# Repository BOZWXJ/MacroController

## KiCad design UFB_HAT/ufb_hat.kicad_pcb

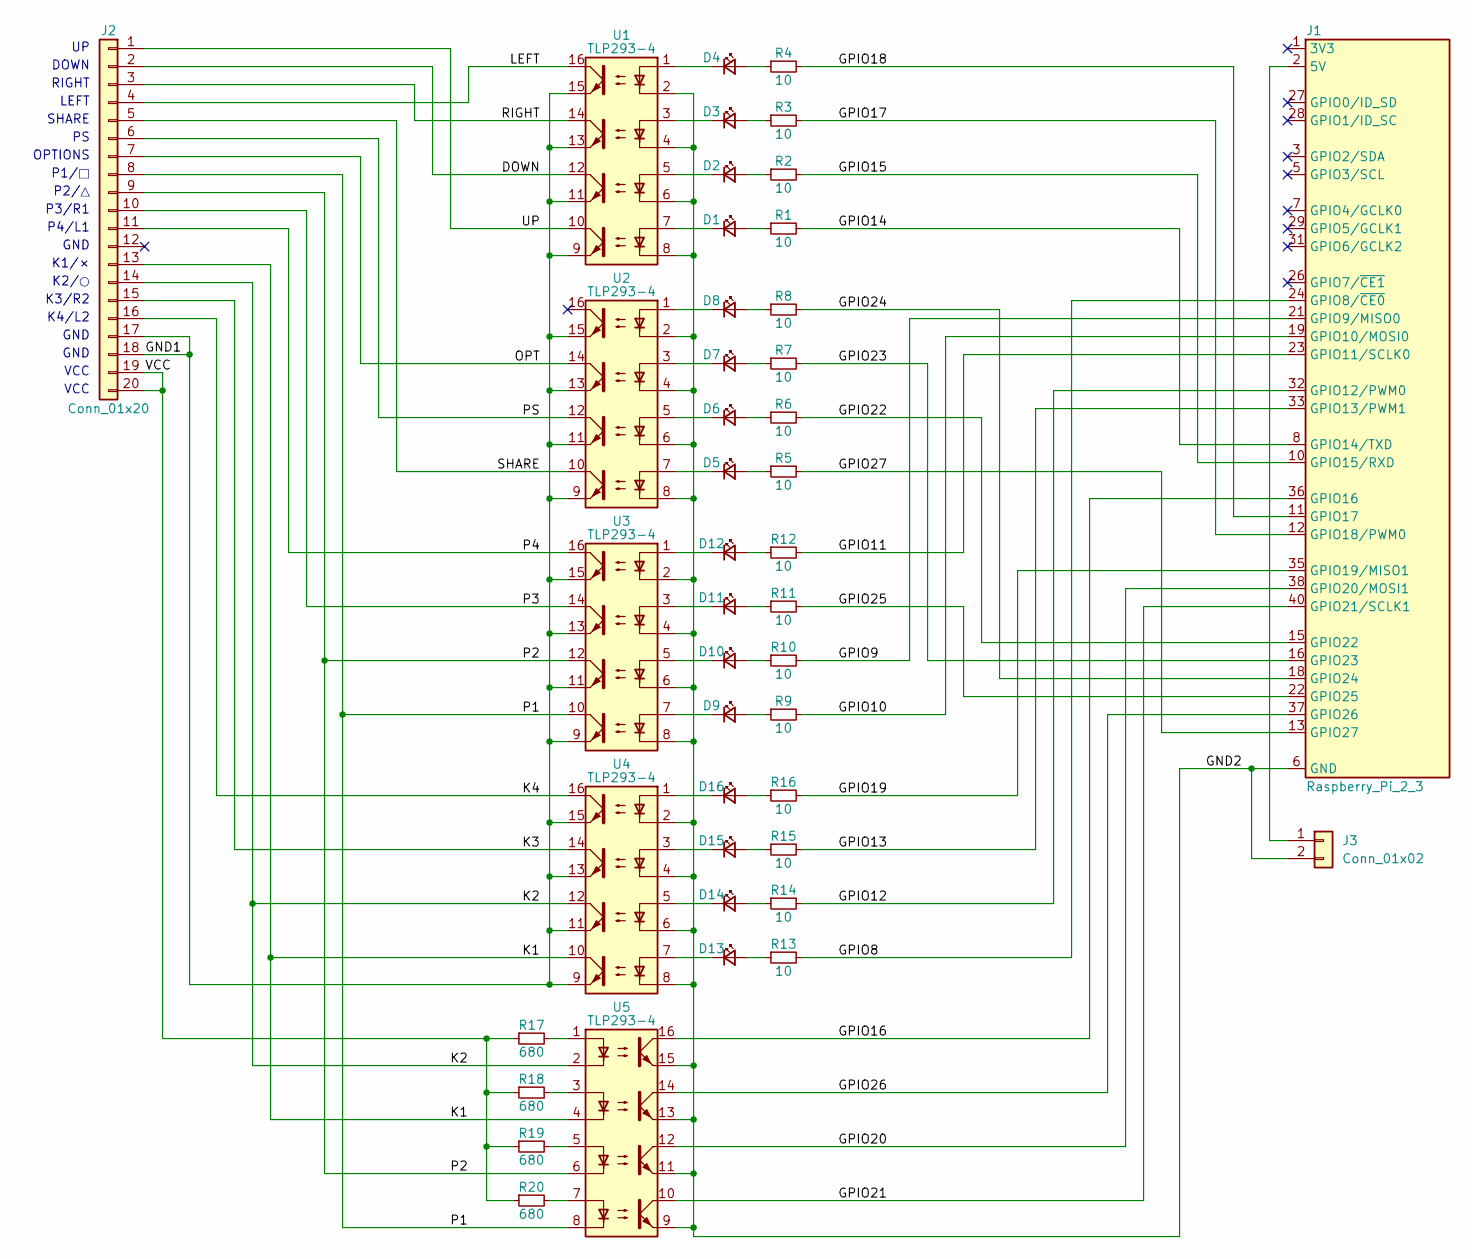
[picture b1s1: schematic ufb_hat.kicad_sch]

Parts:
D1, D2, D3, D4, D5, D6, D7, D8, D9, D10, D11, D12, D13, D14, D15, D16: LED_Small; LED_0603_1608Metric_Pad1.05x0.95mm_HandSolder
J1: Raspberry_Pi_2_3; PinSocket_2x20_P2.54mm_Vertical
J2: Conn_01x20; PinHeader_2x10_P2.54mm_Vertical
J3: Conn_01x02; PinHeader_1x02_P2.54mm_Vertical
R1, R2, R3, R4, R5, R6, R7, R8, R9, R10, R11, R12, R13, R14, R15, R16: 10; R_0603_1608Metric_Pad0.98x0.95mm_HandSolder
R17, R18, R19, R20: 680; R_0603_1608Metric_Pad0.98x0.95mm_HandSolder
U1, U2, U3, U4, U5: TLP293-4; SOIC-16_4.55x10.3mm_P1.27mm

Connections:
/DOWN: J2.2, U1.12
/GND1: J2.17, J2.18, U1.9, U1.11, U1.13, U1.15, U2.9, U2.11, U2.13, U2.15, U3.9, U3.11, U3.13, U3.15, U4.9, U4.11, U4.13, U4.15
/GND2: J1.6 (GND), J1.9 (GND), J1.14 (GND), J1.20 (GND), J1.25 (GND), J1.30 (GND), J1.34 (GND), J1.39 (GND), J3.2, U1.2, U1.4, U1.6, U1.8, U2.2, U2.4, U2.6, U2.8, U3.2, U3.4, U3.6, U3.8, U4.2, U4.4, U4.6, U4.8, U5.9, U5.11, U5.13, U5.15
/GPIO8: J1.24 (GPIO8/~CE0), R13.2
/GPIO9: J1.21 (GPIO9/MISO0), R10.2
/GPIO10: J1.19 (GPIO10/MOSI0), R9.2
/GPIO11: J1.23 (GPIO11/SCLK0), R12.2
/GPIO12: J1.32 (GPIO12/PWM0), R14.2
/GPIO13: J1.33 (GPIO13/PWM1), R15.2
/GPIO14: J1.8 (GPIO14/TXD), R1.2
/GPIO15: J1.10 (GPIO15/RXD), R2.2
/GPIO16: J1.36 (GPIO16), U5.16
/GPIO17: J1.12 (GPIO18/PWM0), R3.2
/GPIO18: J1.11 (GPIO17), R4.2
/GPIO19: J1.35 (GPIO19/MISO1), R16.2
/GPIO20: J1.38 (GPIO20/MOSI1), U5.12
/GPIO21: J1.40 (GPIO21/SCLK1), U5.10
/GPIO22: J1.15 (GPIO22), R6.2
/GPIO23: J1.16 (GPIO23), R7.2
/GPIO24: J1.18 (GPIO24), R8.2
/GPIO25: J1.22 (GPIO25), R11.2
/GPIO26: J1.37 (GPIO26), U5.14
/GPIO27: J1.13 (GPIO27), R5.2
/K1: J2.13, U4.10, U5.4
/K2: J2.14, U4.12, U5.2
/K3: J2.15, U4.14
/K4: J2.16, U4.16
/LEFT: J2.4, U1.16
/OPT: J2.7, U2.14
/P1: J2.8, U3.10, U5.8
/P2: J2.9, U3.12, U5.6
/P3: J2.10, U3.14
/P4: J2.11, U3.16
/PS: J2.6, U2.12
/RIGHT: J2.3, U1.14
/SHARE: J2.5, U2.10
/UP: J2.1, U1.10
/VCC: J2.19, J2.20, R17.1, R18.1, R19.1, R20.1
unnamed: D1.2 (A), R1.1
unnamed: D1.1 (K), U1.7
unnamed: D2.2 (A), R2.1
unnamed: D2.1 (K), U1.5
unnamed: D3.2 (A), R3.1
unnamed: D3.1 (K), U1.3
unnamed: D4.2 (A), R4.1
unnamed: D4.1 (K), U1.1
unnamed: D5.2 (A), R5.1
unnamed: D5.1 (K), U2.7
unnamed: D6.2 (A), R6.1
unnamed: D6.1 (K), U2.5
unnamed: D7.2 (A), R7.1
unnamed: D7.1 (K), U2.3
unnamed: D8.2 (A), R8.1
unnamed: D8.1 (K), U2.1
unnamed: D9.2 (A), R9.1
unnamed: D9.1 (K), U3.7
unnamed: D10.2 (A), R10.1
unnamed: D10.1 (K), U3.5
unnamed: D11.2 (A), R11.1
unnamed: D11.1 (K), U3.3
unnamed: D12.2 (A), R12.1
unnamed: D12.1 (K), U3.1
unnamed: D13.2 (A), R13.1
unnamed: D13.1 (K), U4.7
unnamed: D14.2 (A), R14.1
unnamed: D14.1 (K), U4.5
unnamed: D15.2 (A), R15.1
unnamed: D15.1 (K), U4.3
unnamed: D16.2 (A), R16.1
unnamed: D16.1 (K), U4.1
unnamed: J1.2 (5V), J1.4 (5V), J3.1
unnamed: R17.2, U5.1
unnamed: R18.2, U5.3
unnamed: R19.2, U5.5
unnamed: R20.2, U5.7

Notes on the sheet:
K4/L2
SHARE
K2/○
VCC
K3/R2
OPTIONS
LEFT
GND
P1/□
P4/L1
RIGHT
K1/×
DOWN
P2/△
P3/R1

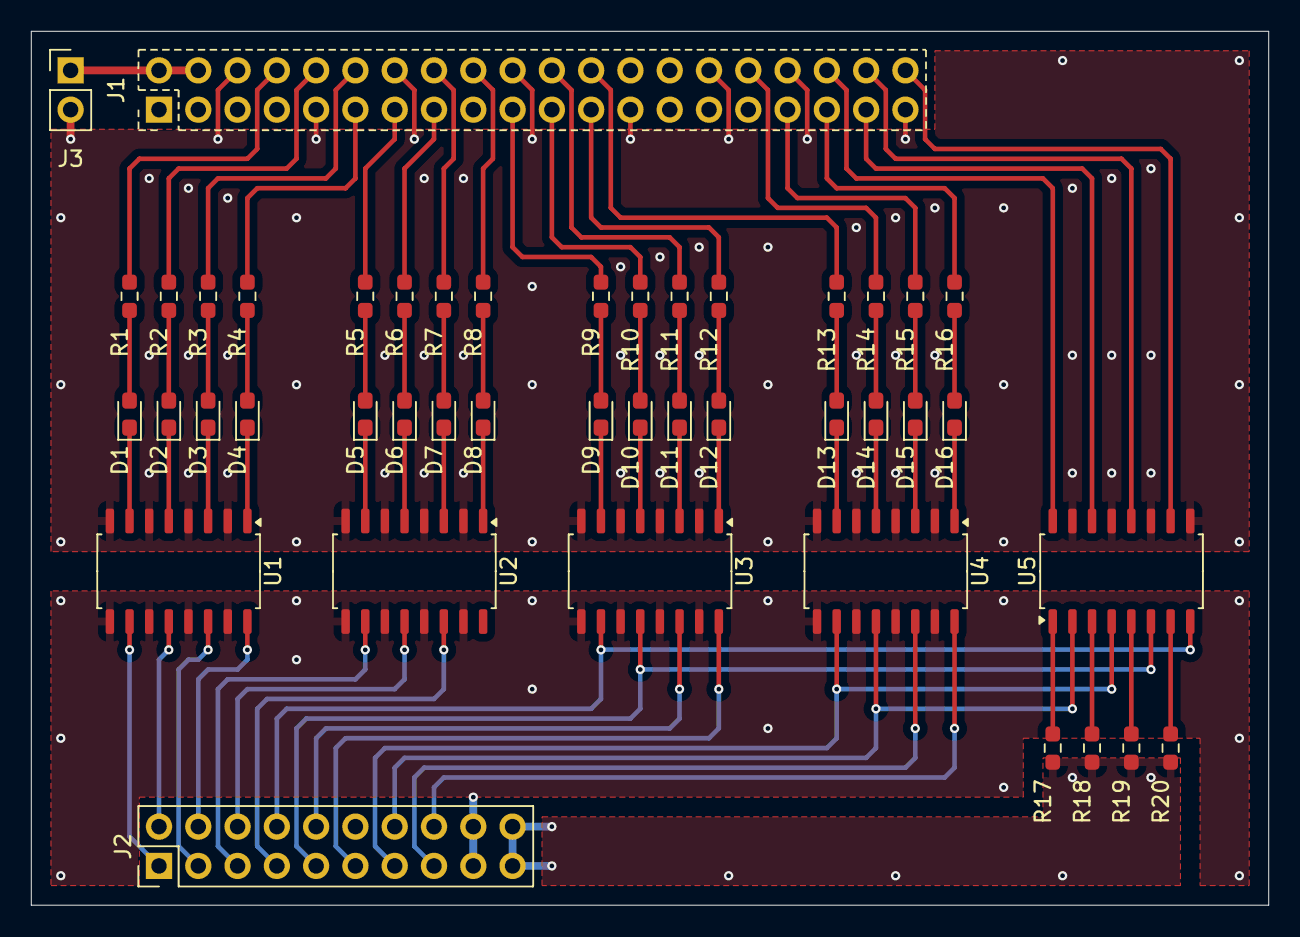
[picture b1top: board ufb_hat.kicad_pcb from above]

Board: 2 copper layers, 80.0 x 56.5 mm, 44 parts (1 on the bottom side), 75 nets.

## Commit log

2025-03-16 debug
2025-03-19 Case
